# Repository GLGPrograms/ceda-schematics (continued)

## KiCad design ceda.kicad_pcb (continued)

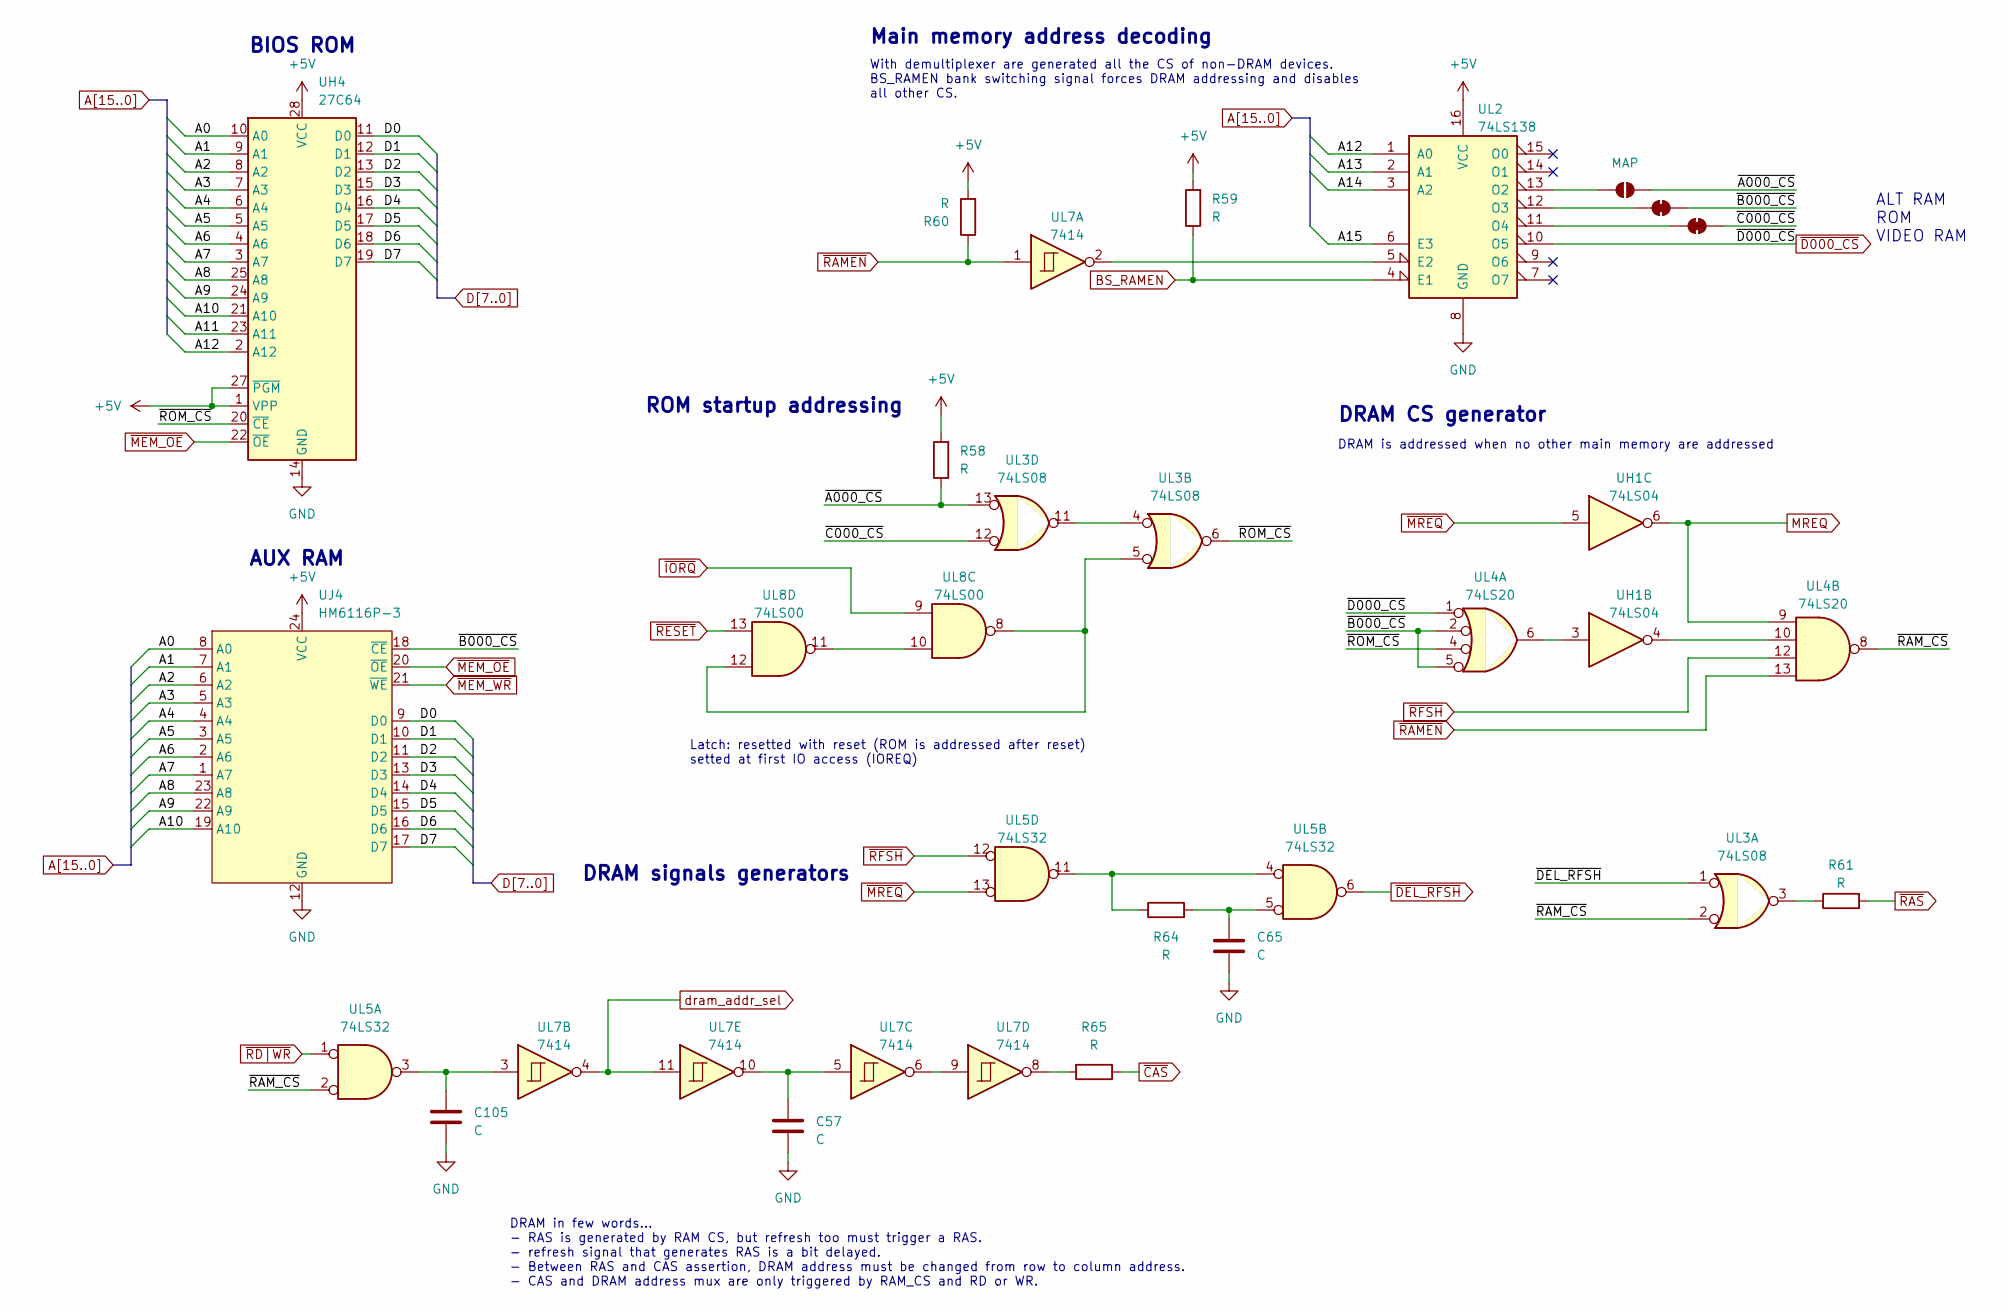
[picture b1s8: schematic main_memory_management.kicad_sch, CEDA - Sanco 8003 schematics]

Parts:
C57, C65, C105: C; C_Disc_D4.3mm_W1.9mm_P5.00mm
JP4: MAP
R58, R59, R60, R61, R64, R65: R; R_Axial_DIN0204_L3.6mm_D1.6mm_P5.08mm_Vertical
UH1: 74LS04; DIP-14_W7.62mm
UH4: 27C64; DIP-28_W15.24mm
UJ4: HM6116P-3; DIP-24_W15.24mm
UL2: 74LS138; DIP-16_W7.62mm
UL3: 74LS08; DIP-14_W7.62mm
UL4: 74LS20; DIP-14_W7.62mm
UL5: 74LS32; DIP-14_W7.62mm
UL7: 7414; DIP-14_W7.62mm
UL8: 74LS00; DIP-14_W7.62mm

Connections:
+5V: R58.2, R59.2, R60.2, UH4.1 (VPP), UH4.27 (~PGM), UH4.28 (VCC), UJ4.24 (VCC), UL2.16 (VCC); also elsewhere on the board
/MainMemoryManagement/~A000_CS: JP4.2 (B), R58.1, UL3.13
/MainMemoryManagement/~B000_CS: JP4.4 (D), UJ4.18 (~CE), UL4.2, UL4.5
/MainMemoryManagement/~C000_CS: JP4.6 (F), UL3.12
/MainMemoryManagement/~RAM_CS: UL3.2, UL4.8, UL5.2
/MainMemoryManagement/~ROM_CS: UH4.20 (~CE), UL3.6, UL4.4
A0: UH4.10 (A0), UJ4.8 (A0); also elsewhere on the board
A1: UH4.9 (A1), UJ4.7 (A1); also elsewhere on the board
A2: UH4.8 (A2), UJ4.6 (A2); also elsewhere on the board
A3: UH4.7 (A3), UJ4.5 (A3); also elsewhere on the board
A4: UH4.6 (A4), UJ4.4 (A4); also elsewhere on the board
A5: UH4.5 (A5), UJ4.3 (A5); also elsewhere on the board
A6: UH4.4 (A6), UJ4.2 (A6); also elsewhere on the board
A7: UH4.3 (A7), UJ4.1 (A7); also elsewhere on the board
A8: UH4.25 (A8), UJ4.23 (A8); also elsewhere on the board
A9: UH4.24 (A9), UJ4.22 (A9); also elsewhere on the board
A10: UH4.21 (A10), UJ4.19 (A10); also elsewhere on the board
A11: UH4.23 (A11); also elsewhere on the board
A12: UH4.2 (A12), UL2.1 (A0); also elsewhere on the board
A13: UL2.2 (A1); also elsewhere on the board
A14: UL2.3 (A2); also elsewhere on the board
A15: UL2.6 (E3); also elsewhere on the board
BS_RAMEN: R59.1, UL2.4 (E1); also elsewhere on the board
D0: UH4.11 (D0), UJ4.9 (D0); also elsewhere on the board
D1: UH4.12 (D1), UJ4.10 (D1); also elsewhere on the board
D2: UH4.13 (D2), UJ4.11 (D2); also elsewhere on the board
D3: UH4.15 (D3), UJ4.13 (D3); also elsewhere on the board
D4: UH4.16 (D4), UJ4.14 (D4); also elsewhere on the board
D5: UH4.17 (D5), UJ4.15 (D5); also elsewhere on the board
D6: UH4.18 (D6), UJ4.16 (D6); also elsewhere on the board
D7: UH4.19 (D7), UJ4.17 (D7); also elsewhere on the board
GND: C57.2, C65.2, C105.2, UH4.14 (GND), UJ4.12 (GND), UL2.8 (GND); also elsewhere on the board
MREQ: UH1.6, UL4.9; also elsewhere on the board
unnamed: C57.1, UL7.5, UL7.10
unnamed: C65.1, R64.2, UL5.5
unnamed: C105.1, UL5.3, UL7.3
unnamed: JP4.1 (A), UL2.13 (O2)
unnamed: JP4.3 (C), UL2.12 (O3)
unnamed: JP4.5 (E), UL2.11 (O4)
unnamed: R61.1, UL3.3
unnamed: R64.1, UL5.4, UL5.11
unnamed: R65.2, UL7.8
unnamed: UH1.3, UL4.6
unnamed: UH1.4, UL4.10
unnamed: UL2.5 (E2), UL7.2
unnamed: UL3.5, UL8.8, UL8.12
unnamed: UL3.4, UL3.11
unnamed: UL7.6, UL7.9
unnamed: UL8.10, UL8.11
dram_addr_sel: UL7.4, UL7.11; also elsewhere on the board
~CAS: R65.1; also elsewhere on the board
~D000_CS: UL2.10 (O5), UL4.1; also elsewhere on the board
~DEL_RFSH: UL3.1, UL5.6
~IORQ: UL8.9; also elsewhere on the board
~MEM_OE: UH4.22 (~OE), UJ4.20 (~OE); also elsewhere on the board
~MEM_WR: UJ4.21 (~WE); also elsewhere on the board
~MREQ: UH1.5, UL5.13; also elsewhere on the board
~RAMEN: R60.1, UL4.13, UL7.1; also elsewhere on the board
~RAS: R61.2; also elsewhere on the board
~RD|WR: UL5.1; also elsewhere on the board
~RESET: UL8.13; also elsewhere on the board
~RFSH: UL4.12, UL5.12; also elsewhere on the board

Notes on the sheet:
Latch: resetted with reset (ROM is addressed after reset) setted at first IO access (IOREQ)
ROM startup addressing
DRAM signals generators
BIOS ROM
DRAM CS generator
DRAM in few words... - RAS is generated by RAM CS, but refresh too must trigger a RAS. - refresh signal that generates RAS is a bit delayed. - Between RAS and CAS assertion, DRAM address must be changed from row to column address. - CAS and DRAM address mux are only triggered by RAM_CS and RD or WR.
With demultiplexer are generated all the CS of non-DRAM devices. BS_RAMEN bank switching signal forces DRAM addressing and disables all other CS.
DRAM is addressed when no other main memory are addressed
ALT RAM ROM VIDEO RAM
AUX RAM
Main memory address decoding

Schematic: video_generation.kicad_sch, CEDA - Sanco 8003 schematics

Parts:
C52, C53: 220p; C_Disc_D4.3mm_W1.9mm_P5.00mm
C54: 47p; C_Disc_D4.3mm_W1.9mm_P5.00mm
D2, D5: D; D_A-405_P5.08mm_Vertical_KathodeUp
J3: Conn_02x06_Odd_Even; PinHeader_2x06_P2.54mm_Vertical
R42: 4.7k; R_Axial_DIN0204_L3.6mm_D1.6mm_P5.08mm_Vertical
R56: 2k2; R_Axial_DIN0309_L9.0mm_D3.2mm_P12.70mm_Horizontal
R57: 4k7; R_Axial_DIN0309_L9.0mm_D3.2mm_P12.70mm_Horizontal
R67, R71, R72, R75: R; R_Axial_DIN0204_L3.6mm_D1.6mm_P5.08mm_Vertical
R68, R69, R73, R74: 470; R_Axial_DIN0204_L3.6mm_D1.6mm_P5.08mm_Vertical
R70, R76: 10; R_Axial_DIN0204_L3.6mm_D1.6mm_P5.08mm_Vertical
R7777: R
RCK1: ContrastKnob
TP4: EXT; TestPoint_Plated_Hole_D2.0mm
TP5: TestPoint
TR4: Q_NPN_BCE; TO-92_Inline_Wide
UE7: CRTC; DIP-40_W15.24mm
UE12: 74LS175; DIP-16_W7.62mm
UE13: 74LS04; DIP-14_W7.62mm
UE15: 74LS32; DIP-14_W7.62mm
UF13: 74LS08; DIP-14_W7.62mm
UH11: 74LS273; DIP-20_W7.62mm
UH12: 2732; DIP-24_W15.24mm
UJ12: 28L22; DIP-20_W7.62mm
UJ13: 74LS86; DIP-14_W7.62mm
UJ14: 74LS166; DIP-16_W7.62mm
UJ15: 74LS161; DIP-16_W7.62mm
UK10: 74LS08; DIP-14_W7.62mm
UK11, UK12: 74LS273; DIP-20_W7.62mm
UK13: 74LS00; DIP-14_W7.62mm
UK14: 74LS10; DIP-14_W7.62mm
UK15: 74LS04; DIP-14_W7.62mm
UL9: 74LS109; DIP-16_W7.62mm
UL10: 74S174; DIP-16_W7.62mm
UL11: 74LS393; DIP-14_W7.62mm
UL12: 74S00; DIP-14_W7.62mm
UL13: 74LS38; DIP-14_W7.62mm
XTAL3: Crystal; Crystal_HC18-U_Horizontal_1EP_style2

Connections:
+5V: R42.1, R67.2, R68.1, R69.1, R75.1, R7777.1, TR4.2 (C), UE7.20 (VCC), UE12.1 (~Mr), UE12.16 (VCC), UH11.1 (~Mr), UH11.20 (VCC), UH12.24 (VCC), UJ12.20 (VCC), UJ14.9 (Clr), UJ14.16 (VCC), UJ15.1 (~MR), UJ15.7 (CEP), UJ15.10 (CET), UJ15.16 (VCC), UK11.1 (~Mr), UK11.20 (VCC), UK12.1 (~Mr), UK12.20 (VCC), UL9.2 (J), UL9.3 (~K), UL9.5 (~S), UL10.16 (VCC); also elsewhere on the board
/VideoGeneration/BEAM: J3.4, R76.2
/VideoGeneration/CONTRAST0: J3.12, R70.2, RCK1.2
/VideoGeneration/CONTRAST1: D5.2 (A), J3.11, R72.1, RCK1.1, UL13.6
/VideoGeneration/HSYNC: J3.8, R68.2, UL13.8
/VideoGeneration/PIXEL_CLK: UJ14.7 (Clk), UJ15.2 (CP), UK15.6, UL10.9 (Cp)
/VideoGeneration/ROM_A5: UJ12.17 (A5), UK11.16 (Q6)
/VideoGeneration/ROM_A6: UJ12.18 (A6), UK11.19 (Q7)
/VideoGeneration/ROM_A7: UJ12.19 (A7), UK11.15 (Q5)
/VideoGeneration/ROM_D5: UJ12.12 (D5), UK12.18 (D7)
/VideoGeneration/ROM_D6: UJ12.13 (D6), UK12.17 (D6)
/VideoGeneration/ROM_D7: UJ12.14 (D7), UK12.14 (D5)
/VideoGeneration/VSYNC: J3.7, R69.2, UL13.11
/VideoGeneration/VSYNC_CRTC: UE7.40 (VSYNC), UE13.9, UL9.4 (C)
/VideoGeneration/attr_blink: UK12.5 (Q1), UK13.5
/VideoGeneration/attr_blink_underline: UK12.15 (Q5), UK13.9
/VideoGeneration/attr_cursor: UK12.6 (Q2), UL10.6 (D2)
/VideoGeneration/attr_cursor_reg: UL10.7 (Q2), UL12.4, UL12.12
/VideoGeneration/attr_invert: UJ13.4, UK12.9 (Q3)
/VideoGeneration/attr_show: UK12.19 (Q7), UK14.11
/VideoGeneration/attr_stretch: UF13.2, UK12.12 (Q4)
/VideoGeneration/attr_underline: UK12.16 (Q6), UK13.12
/VideoGeneration/blink timer: UK13.4, UK13.10, UL11.8 (Q3)
/VideoGeneration/char0: UH11.16 (Q6), UH12.4 (A4)
/VideoGeneration/char1: UH11.2 (Q0), UH12.3 (A5)
/VideoGeneration/char2: UH11.19 (Q7), UH12.2 (A6)
/VideoGeneration/char3: UH11.12 (Q4), UH12.1 (A7)
/VideoGeneration/char4: UH11.9 (Q3), UH12.23 (A8)
/VideoGeneration/char5: UH11.6 (Q2), UH12.22 (A9)
/VideoGeneration/char6: UH11.15 (Q5), UH12.19 (A10)
/VideoGeneration/char7: UH11.5 (Q1), UH12.21 (A11)
/VideoGeneration/cl0: UH12.8 (A0), UJ12.6 (D0)
/VideoGeneration/cl1: UH12.7 (A1), UJ12.7 (D1)
/VideoGeneration/cl2: UH12.6 (A2), UJ12.8 (D2)
/VideoGeneration/cl3: UH12.5 (A3), UJ12.9 (D3)
/VideoGeneration/crt3: J3.3, R75.2, UL13.1
/VideoGeneration/crt5: J3.5, UL12.3, UL13.2
/VideoGeneration/cudisp: UE7.19 (CUDISP), UE12.12 (D2)
/VideoGeneration/cudisp_int: UE12.10 (Q2), UE12.13 (D3)
/VideoGeneration/cudisp_reg: UE12.15 (Q3), UJ13.10
/VideoGeneration/disptmg: UE7.18 (DISPTMG), UE12.4 (D0), UK10.4
/VideoGeneration/disptmg_ancorpiureg: UK10.1, UL10.5 (Q1)
/VideoGeneration/disptmg_int: UE12.2 (Q0), UE12.5 (D1)
/VideoGeneration/dot pattern: UJ14.13 (Qh), UK14.10
/VideoGeneration/pixel: UJ13.8, UL10.3 (D0)
/VideoGeneration/pixel_reg: UK10.2, UL10.2 (Q0)
/VideoGeneration/pixel_valid: UK10.3, UL12.2, UL12.13
/VideoGeneration/ra0: UE7.38 (RA0), UJ12.1 (A0)
/VideoGeneration/ra1: UE7.37 (RA1), UJ12.2 (A1)
/VideoGeneration/ra2: UE7.36 (RA2), UJ12.3 (A2)
/VideoGeneration/ra3: UE7.35 (RA3), UJ12.4 (A3)
/VideoGeneration/ra4: UE7.34 (RA4), UJ12.5 (A4)
/VideoGeneration/stretch: UK11.12 (Q4), UK12.13 (D4), UK15.1
/VideoGeneration/~CHAR_EN: UJ14.15 (PE), UJ15.9 (~PE), UK12.11 (Cp), UK15.10
/VideoGeneration/~VSYNC_CRTC: UE13.8, UL11.1 (CP), UL13.12, UL13.13
/VideoGeneration/~cudisp_reg: UE12.14 (~Q3), UL12.5
/VideoGeneration/~pixel_cursor: J3.6, UL12.11, UL13.4, UL13.5
A0: UE7.24 (RS); also elsewhere on the board
CRTC_CLK: TP5.1, UE7.21 (CLK), UJ15.12 (Q2), UK15.9; also elsewhere on the board
D0: UE7.33 (D0); also elsewhere on the board
D1: UE7.32 (D1); also elsewhere on the board
D2: UE7.31 (D2); also elsewhere on the board
D3: UE7.30 (D3); also elsewhere on the board
D4: UE7.29 (D4); also elsewhere on the board
D5: UE7.28 (D5); also elsewhere on the board
D6: UE7.27 (D6); also elsewhere on the board
D7: UE7.26 (D7); also elsewhere on the board
FRAME_SYNC: UL9.6 (Q); also elsewhere on the board
GND: C52.2, C53.2, J3.1, J3.2, J3.9, J3.10, R57.1, R70.1, R71.2, R72.2, R73.2, R74.2, UE7.1 (VSS), UE12.8 (GND), UH11.10 (GND), UH12.12 (GND), UH12.18 (~CE), UH12.20 (~OE), UJ12.10 (GND), UJ12.15 (~G1), UJ12.16 (~G2), UJ14.1 (Ds), UJ14.8 (GND), UJ15.3 (D0), UJ15.4 (D1), UJ15.5 (D2), UJ15.8 (GND), UK11.10 (GND), UK12.10 (GND), UL10.8 (GND), UL11.2 (MR), UL11.12 (MR); also elsewhere on the board
unnamed: C52.1, C54.2, R56.2, R57.2, UK15.3
unnamed: C53.1, R56.1, UK15.4, UK15.5, XTAL3.2
unnamed: C54.1, XTAL3.1
unnamed: D2.2 (A), R71.1, UL13.3
unnamed: D2.1 (K), D5.1 (K), R73.1, R7777.2, TR4.3 (B)
unnamed: R74.1, R76.1, TR4.1 (E)
unnamed: UE7.23 (E), UE13.10
unnamed: UE7.39 (HSYNC), UE13.1
unnamed: R42.2, UE7.3 (LPSTB)
unnamed: UE13.2, UL13.9, UL13.10
unnamed: UE13.11, UE13.12
unnamed: UE13.13, UK13.3
unnamed: UF13.1, UK15.12
unnamed: UH12.9 (D0), UJ14.2 (A)
unnamed: UH12.10 (D1), UJ14.3 (B)
unnamed: UH12.11 (D2), UJ14.4 (C)
unnamed: UH12.13 (D3), UJ14.5 (D)
unnamed: UH12.14 (D4), UJ14.10 (E)
unnamed: UH12.15 (D5), UJ14.11 (F)
unnamed: UH12.16 (D6), UJ14.12 (G)
unnamed: UH12.17 (D7), UJ14.14 (H)
unnamed: UJ13.5, UK14.6
unnamed: UJ13.6, UJ13.9
unnamed: UF13.3, UJ14.6 (CE)
unnamed: UJ15.6 (D3), UK15.2
unnamed: UJ15.15 (TC), UK15.11
unnamed: UK10.6, UK11.13 (D4)
unnamed: TP4.1, UK11.2 (Q0)
unnamed: UK11.5 (Q1), UK12.4 (D1)
unnamed: UK11.6 (Q2), UK12.7 (D2)
unnamed: UK11.9 (Q3), UK12.8 (D3)
unnamed: UK13.6, UK14.9
unnamed: UK13.11, UK14.4
unnamed: UK13.8, UK13.13
unnamed: UK14.3, UK14.5, UK14.8
unnamed: UE15.8, UL9.1 (~R)
unnamed: R67.1, UL10.1 (~Mr)
unnamed: UL11.3 (Q0), UL11.13 (CP)
unnamed: UL12.1, UL12.6
VMA0: UE7.4 (MA0); also elsewhere on the board
VMA1: UE7.5 (MA1); also elsewhere on the board
VMA2: UE7.6 (MA2); also elsewhere on the board
VMA3: UE7.7 (MA3); also elsewhere on the board
VMA4: UE7.8 (MA4); also elsewhere on the board
VMA5: UE7.9 (MA5); also elsewhere on the board
VMA6: UE7.10 (MA6); also elsewhere on the board
VMA7: UE7.11 (MA7); also elsewhere on the board
VMA8: UE7.12 (MA8); also elsewhere on the board
VMA9: UE7.13 (MA9); also elsewhere on the board
VMA10: UE7.14 (MA10); also elsewhere on the board
attrmd0: UK11.8 (D3); also elsewhere on the board
attrmd1: UK11.4 (D1); also elsewhere on the board
attrmd2: UK11.7 (D2); also elsewhere on the board
attrmd3: UK10.5; also elsewhere on the board
attrmd4: UK11.17 (D6); also elsewhere on the board
attrmd5: UK11.18 (D7); also elsewhere on the board
attrmd6: UK11.14 (D5); also elsewhere on the board
attrmd7: UK11.3 (D0); also elsewhere on the board
chmd0: UH11.17 (D6); also elsewhere on the board
chmd1: UH11.3 (D0); also elsewhere on the board
chmd2: UH11.18 (D7); also elsewhere on the board
chmd3: UH11.13 (D4); also elsewhere on the board
chmd4: UH11.8 (D3); also elsewhere on the board
chmd5: UH11.7 (D2); also elsewhere on the board
chmd6: UH11.14 (D5); also elsewhere on the board
chmd7: UH11.4 (D1); also elsewhere on the board
disptmg_reg: UE12.7 (Q1), UL10.4 (D1); also elsewhere on the board
half_pxclk: UJ15.14 (Q0), UK15.13; also elsewhere on the board
quart_pxclk: UJ15.13 (Q1); also elsewhere on the board
~CRTC_CLK: UE12.9 (Cp), UH11.11 (Cp), UK11.11 (Cp), UK15.8; also elsewhere on the board
~CRTC_CS: UE7.25 (~CS), UE15.9; also elsewhere on the board
~IO_OE: UE15.10, UK13.2; also elsewhere on the board
~IO_WR: UE7.22 (R/~W), UK13.1; also elsewhere on the board
~RESET: UE7.2 (~RES); also elsewhere on the board

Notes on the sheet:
Always enabled and never resetted
underline is generated by attribute index (attributes 4-6). It can add underline, overline, both, or a blinking underline (combined with blink_underline signal). Note that "underline" is not affected by "blink" nor "show", hereby the presence of blink_underline.
Toggle pixels when cursor has to be shown. If characher is inverted, cursor is inverted too.
Pixel clock generator
Counter
Character Line Index
Last stage of pipeline: pixel is registered. To keep signals in sync with the pipeline, the signals used in this last stage are delayed. Why cudisp is not delayed? We don't know.
Then, character is sampled for each character in J14 shift register. Attributes are sampled for each character in register K12. Note: ~{CHAR_EN} period is doubled when horizontal stretch is requested. For this reason both attributes and character must be freezed with PIXEL_EN.
Invert is attribute 0: when is set, frame is displayed in inverted colors.
Wired OR. Transistor base is pulled up (i.e. BEAM is pulled up) if L13B is HIGH or L13A is HIGH.
All RAMs outputs (both char and attr) are syncronized on negative edge of CRTC_CLK.
blink is attribute 1: - when 0, it gates blink_timer and dot_pattern is not affected. - when 1, blink_timer can gate dot_pattern, making the character appear and disappear. blink_timer is a square wave obtained from VSYNC / 32 ~ 1.28s
Character clock generator
This latch is used to generate a syncronization signal, set by the VSYNC from CRTC, resetted by a read access to CRTC from Z80.
Character Line Pattern
Both disptmg and cudisp must be delayed to be in sync with the pipeline. At the output of J14, a double CRTC_CLK delay is needed.
(pixel_reg and disptmg) and attr_cursor or (pixel_reg and disptmg) and (~attr_cursor or cudisp)
show is generated by attribute index (attributes 4-6). It is always set, unless if index=100.
Raster address
1/32 VSYNC ~ 1.28s
Blink generator
Attribute Memory Data
Char ROM
Character Memory Data
1.875MHz
Video memory Address
All video data occurring during blanking time must be ignored. DISPTMG is 0 during blanking time.
Handling horizontal stretch attribute: - When stretch attribute is 0, the shift register is always enabled; - When stretch attribute is 1, the shift register is enabled one clock in two.
174

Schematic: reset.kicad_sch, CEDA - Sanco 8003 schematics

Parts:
C12, C14, C15, C36: C; C_Disc_D4.3mm_W1.9mm_P5.00mm
C40: 10n; C_Disc_D4.3mm_W1.9mm_P5.00mm
C55: C_Polarized; CP_Radial_D5.0mm_P2.50mm
D3: D; D_A-405_P5.08mm_Vertical_KathodeUp
J4: MAINCLK
R17, R023, R41, R44, R63: R; R_Axial_DIN0204_L3.6mm_D1.6mm_P5.08mm_Vertical
R55: 10k; R_Axial_DIN0309_L9.0mm_D3.2mm_P12.70mm_Horizontal
UA6: 74LS161; DIP-16_W7.62mm
UA7: 74LS04; DIP-14_W7.62mm
UD3: 7406; DIP-14_W7.62mm
UD14: 74LS32; DIP-14_W7.62mm
UF16: 74LS04; DIP-14_W7.62mm
UH15: 74LS74; DIP-14_W7.62mm
UH16: 74LS123; DIP-16_W7.62mm
UL7: 7414; DIP-14_W7.62mm
XTAL1: 16M; Crystal_HC18-U_Vertical

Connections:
+5V: C12.2, C15.2, D3.1 (K), R41.1, R44.1, R55.1, R63.2, UA6.1 (~MR), UA6.9 (~PE), UA6.16 (VCC), UH15.2 (D), UH15.4 (~S), UH16.11 (Clr); also elsewhere on the board
/Reset/BTN_RESET: UD14.9, UH16.5 (Q)
/Reset/POR: UD14.10, UL7.12
CPU_CLK: UA7.12; also elsewhere on the board
EXBUS_CLK: UA7.10; also elsewhere on the board
FDC_CLK: UA7.6; also elsewhere on the board
GND: C36.2, C55.2, R023.2, UA6.3 (D0), UA6.4 (D1), UA6.5 (D2), UA6.6 (D3), UA6.8 (GND), UH16.9 (A); also elsewhere on the board
unnamed: C12.1, R17.2, UA7.1, UA7.4, XTAL1.1
unnamed: C14.1, XTAL1.2
unnamed: C14.2, C15.1, R17.1, R023.1, UA7.3
unnamed: C55.1, D3.2 (A), R63.1, UL7.13
unnamed: J4.4 (A0), UA7.5
unnamed: J4.2 (A1), UA6.14 (Q0)
unnamed: J4.1 (B1), UA6.13 (Q1), UA7.11, UA7.13
unnamed: UA6.2 (CP), UA7.2
unnamed: UD3.9, UD14.8
unnamed: UF16.6, UH15.3 (C)
unnamed: UH15.5 (Q), UH16.10 (B)
unnamed: UF16.12, UH15.1 (~R)
unnamed: C40.2, UH16.6 (Cext)
unnamed: C40.1, R55.2, UH16.7 (RCext)
RESET: UF16.10; also elsewhere on the board
~M1: UF16.5; also elsewhere on the board
~RESET_BTN: C36.1, R44.2, UF16.13; also elsewhere on the board
~RESET: R41.2, UD3.8, UF16.11; also elsewhere on the board

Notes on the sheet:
Generates a single reset pulse when signal on B input is asserted. Reset pulse width is 30us long.
Reset circuit
Button reset is syncronized with Z80 opcode fetch (M1)
This should be just R23, but KiCAD complains about it
Power On Reset POR is asserted while capacitor voltage is below VIH of 7414. Diode makes the capacitor discharge faster on power off.
Pushbutton signal from daughterboard
Main clock circuit

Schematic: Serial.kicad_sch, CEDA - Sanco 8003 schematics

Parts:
C16, C17, C18, C19, C29, C30, C31: 330p; C_Disc_D4.3mm_W1.9mm_P5.00mm
C28: 330p; C_Disc_D4.3mm_W1.9mm_P5.00mm; not fitted
J5: SIOCLK; PinHeader_2x03_P2.54mm_Vertical
JP3: KB_SEL; PinHeader_2x01_P2.54mm_Vertical
R40, R79: 4k7; R_Axial_DIN0204_L3.6mm_D1.6mm_P5.08mm_Vertical
UA15: SN75189; DIP-14_W7.62mm
UB9: 74LS04; DIP-14_W7.62mm
UC2: 7417; DIP-14_W7.62mm
UC10: Z8440/2 (SIO/2); DIP-40_W15.24mm
UC15: DIP-14_W7.62mm
UD14: 74LS32; DIP-14_W7.62mm
UD15, UD16: SN75188; DIP-14_W7.62mm

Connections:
+5V: R40.1, R79.2; also elsewhere on the board
+12V: UD15.14 (VCC+), UD16.14 (VCC+); also elsewhere on the board
-12V: UD15.1 (VCC-), UD16.1 (VCC-); also elsewhere on the board
/Serial/RxCA: J5.2 (A0), UC10.13 (~RxCA)
/Serial/RxCA': J5.1 (A1), UA15.11
/Serial/RxDA: UC10.12 (RxDA), UC15.3
/Serial/RxDB: UC10.29 (RxDB), UD14.11
/Serial/TxCA: J5.4 (B0), J5.6 (C0), UC10.14 (~TxCA)
/Serial/TxCA': J5.3 (B1), UA15.8
/Serial/TxDA: UC10.15 (TxDA), UD15.2
/Serial/TxDB: UC10.26 (TxDB), UD14.1, UD14.4
/Serial/~CTSA: UC10.18 (~CTSA), UC15.6
/Serial/~CTSB: UA15.6, UC10.23 (~CTSB)
/Serial/~DCDA: UC10.19 (~DCDA), UC15.8
/Serial/~DCDB: UA15.3, UC10.22 (~DCDB)
/Serial/~DTRA: UC10.16 (~DTRA), UD15.9, UD15.10
/Serial/~DTRB: UB9.9, UC10.25 (~DTRB), UD14.2
/Serial/~RTSA: UC10.17 (~RTSA), UD15.4, UD15.5
A0: UC10.33 (C/~D); also elsewhere on the board
A1: UC10.34 (B/~A); also elsewhere on the board
CPU_CLK: UC10.20 (CLK); also elsewhere on the board
D0: UC10.40 (D0); also elsewhere on the board
D1: UC10.1 (D1); also elsewhere on the board
D2: UC10.39 (D2); also elsewhere on the board
D3: UC10.2 (D3); also elsewhere on the board
D4: UC10.38 (D4); also elsewhere on the board
D5: UC10.3 (D5); also elsewhere on the board
D6: UC10.37 (D6); also elsewhere on the board
D7: UC10.4 (D7); also elsewhere on the board
GND: C16.1, C17.1, C18.1, C19.1, C28.1, C29.1, C30.1, C31.1, UC10.31 (GND), UD15.7 (GND), UD16.7 (GND); also elsewhere on the board
KBD_CLK: UC10.27 (~TxCB), UC10.28 (~RxCB); also elsewhere on the board
KBD_RX: JP3.2 (B), R79.1, UC2.6; also elsewhere on the board
KBD_TX: JP3.1 (A), R40.2, UD14.12, UD14.13; also elsewhere on the board
unnamed: C16.2, UA15.9
unnamed: C17.2, UA15.2
unnamed: C18.2, UA15.12
unnamed: C19.2, UA15.5
unnamed: C28.2, UC15.12
unnamed: C29.2, UC15.9
unnamed: C30.2, UC15.5
unnamed: C31.2, UC15.2
unnamed: UB9.8, UD14.5
unnamed: UC2.5, UD14.3
unnamed: UD14.6, UD16.2
PRNT_1: UD16.3; also elsewhere on the board
PRNT_3: UA15.4; also elsewhere on the board
PRNT_4: UA15.1; also elsewhere on the board
SER_2: UD15.3; also elsewhere on the board
SER_3: UC15.1; also elsewhere on the board
SER_4: UD15.6; also elsewhere on the board
SER_5: UC15.4; also elsewhere on the board
SER_6: UC15.10; also elsewhere on the board
SER_15: UA15.10; also elsewhere on the board
SER_17: UA15.13; also elsewhere on the board
SER_20: UD15.8; also elsewhere on the board
SER_24: UD15.11; also elsewhere on the board
SER_CLK: J5.5 (C1), UD15.12, UD15.13; also elsewhere on the board
~IE_0: UC10.6 (IEI)
~IE_1: UC10.7 (IEO); also elsewhere on the board
~INT: UC10.5 (~INT); also elsewhere on the board
~IORQ: UC10.36 (~IORQ); also elsewhere on the board
~M1: UC10.8 (~M1); also elsewhere on the board
~RD: UC10.32 (~RD); also elsewhere on the board
~RESET: UC10.21 (~RESET); also elsewhere on the board
~SIO_CS: UC10.35 (~CE); also elsewhere on the board

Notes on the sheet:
RS-232 UART
153.6 kHz
Open Collector
Standard RS-232 with +/-12V logic levels, hardware flux control support, syncronous serial support. As default, UART timebase is generated by CTC and provided both to SIO (RxCA and TxCA) and to device (TxCA''). This setting may be changed by using SIOCLK jumpers.
Supplementary UART
Keyboard UART
CEDA keyboard UART has a double usage, since when DTR is asserted the communication with keyboard is disabled and data is transmitted on PRNT connector. The device connected to PRNT may signal its presence (DCD) or suspend data flow (CTS). The device can't send data to the CEDA, so except for the f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
CEDA keyboard communicates by TTL UART, half duplex, open collector. Timebase is generated by CTC, as default set to 9600 baud. RX and TX lines are shorted on board. TX is disabled when DTR is asserted.

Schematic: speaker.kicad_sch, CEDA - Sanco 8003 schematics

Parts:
C22: 4.7u; CP_Radial_D5.0mm_P2.50mm
C23, C25, C32: 10n; C_Disc_D4.3mm_W1.9mm_P5.00mm
LS0: Speaker
R36, R38: 37k; R_Axial_DIN0204_L3.6mm_D1.6mm_P5.08mm_Vertical
R37: 33k; R_Axial_DIN0204_L3.6mm_D1.6mm_P5.08mm_Vertical
R78: 33; R_Axial_DIN0309_L9.0mm_D3.2mm_P12.70mm_Horizontal
RM2: R_Network08; R_Array_SIP9
SP-Plug1: Molex_KK-254_AE-6410-02A_1x02_P2.54mm_Vertical
SP-Socket1: SpeakerConnector
SW1: SW_DIP_x08; SW_DIP_SPSTx08_Slide_9.78x22.5mm_W7.62mm_P2.54mm
UA11: 74LS541; DIP-20_W7.62mm
UC7: LM556; DIP-14_W7.62mm
UD8, UD9: 74LS138; DIP-16_W7.62mm
UF16: 74LS04; DIP-14_W7.62mm

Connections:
+5V: R37.1, R38.1, R78.2, RM2.1 (common), UA11.20 (VCC), UC7.4 (R), UC7.14 (VCC), UD8.16 (VCC), UD9.16 (VCC); also elsewhere on the board
/IO space/~DIPSW_CS: UA11.1 (G1), UD8.12 (O3)
/IO space/~SPEAKER_CS: UC7.6 (TR), UD8.10 (O5)
A1: UD8.1 (A0); also elsewhere on the board
A2: UD8.2 (A1); also elsewhere on the board
A3: UD8.3 (A2); also elsewhere on the board
A4: UD9.1 (A0); also elsewhere on the board
A5: UD9.2 (A1); also elsewhere on the board
A6: UD9.3 (A2); also elsewhere on the board
A7: UD9.6 (E3); also elsewhere on the board
D0: UA11.18 (Y0); also elsewhere on the board
D1: UA11.17 (Y1); also elsewhere on the board
D2: UA11.16 (Y2); also elsewhere on the board
D3: UA11.15 (Y3); also elsewhere on the board
D4: UA11.14 (Y4); also elsewhere on the board
D5: UA11.13 (Y5); also elsewhere on the board
D6: UA11.12 (Y6); also elsewhere on the board
D7: UA11.11 (Y7); also elsewhere on the board
GND: C22.2, C23.1, C25.1, C32.2, SW1.1, SW1.2, SW1.3, SW1.4, SW1.5, SW1.6, SW1.7, SW1.8, UA11.10 (GND), UC7.7 (GND), UD8.8 (GND), UD9.4 (E1), UD9.5 (E2), UD9.8 (GND); also elsewhere on the board
unnamed: LS0.1, SP-Socket1.2
unnamed: LS0.2, SP-Socket1.1
unnamed: RM2.2 (R1), SW1.9, UA11.2 (A0)
unnamed: RM2.3 (R2), SW1.10, UA11.3 (A1)
unnamed: RM2.4 (R3), SW1.11, UA11.4 (A2)
unnamed: RM2.5 (R4), SW1.12, UA11.5 (A3)
unnamed: RM2.6 (R5), SW1.13, UA11.6 (A4)
unnamed: RM2.7 (R6), SW1.14, UA11.7 (A5)
unnamed: RM2.8 (R7), SW1.15, UA11.8 (A6)
unnamed: SP-Plug1.1, UC7.9 (Q)
unnamed: R78.1, SP-Plug1.2
unnamed: C25.2, UC7.3 (CV)
unnamed: C22.1, R38.2, UC7.1 (DIS), UC7.2 (THR)
unnamed: UC7.5 (Q), UC7.10 (R)
unnamed: C23.2, UC7.11 (CV)
unnamed: R36.2, R37.2, UC7.13 (DIS)
unnamed: C32.1, R36.1, UC7.8 (TR), UC7.12 (THR)
unnamed: UD8.5 (E2), UD9.10 (O5)
unnamed: UD8.6 (E3), UF16.4
disptmg_reg: UA11.9 (A7); also elsewhere on the board
~CRTC_CS: UD9.13 (O2); also elsewhere on the board
~CTC_CS: UD9.9 (O6); also elsewhere on the board
~FDC_CS: UD9.11 (O4); also elsewhere on the board
~FDC_TC: UD8.9 (O6); also elsewhere on the board
~GPIO_CS: UD9.15 (O0); also elsewhere on the board
~IORQ: UF16.3; also elsewhere on the board
~MysteriousTrigger_CS: UD8.11 (O4); also elsewhere on the board
~PerrorReset_CS: UD8.7 (O7); also elsewhere on the board
~PrinterReset_CS: UD8.14 (O1); also elsewhere on the board
~PrinterSet_CS: UD8.15 (O0); also elsewhere on the board
~RD|WR: UD8.4 (E1); also elsewhere on the board
~RD: UA11.19 (G2); also elsewhere on the board
~SIO_CS: UD9.12 (O3); also elsewhere on the board

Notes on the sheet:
Big IO
0xDC FDC Terminal Count
DIP switch IO = 0xD6
IO address space multiplexing Each IO device has 4 address bits reserved. The other 4 bits are used to partition the addressing space. Small IO addressing space has 1 bit for each peripheral (i.e. 2 address) but most of them use only one address.
DIP Switch is set to 0x0E. It contains the configuration of the SIO baudrate.
0xD- small IO
0xD6 DIP Switch
f = 1.3kHz
0xDA speaker
t = 120ms
0x9- unused?
0xF- unused?
0xE- CTC
0xA- CRTC
Speaker IO = 0xDA
0xDE parity error reset
0xD2 handshake on PRN connector (reset)
0xD8 trigger CTC
0xD0 handshake on PRN connector (set)
0xD4 unused?
Small IO
0x8- 8255 GPIO
0xC- FDC
0xB- SIO

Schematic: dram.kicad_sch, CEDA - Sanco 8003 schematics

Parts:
C106: C; C_Disc_D4.3mm_W1.9mm_P5.00mm
PARITY1: LED; LED_D3.0mm
R46, R62: R; R_Axial_DIN0204_L3.6mm_D1.6mm_P5.08mm_Vertical
R47, R48, R49, R50, R51, R52, R53, R54: R_Small; R_Axial_DIN0204_L3.6mm_D1.6mm_P5.08mm_Vertical
R66: 470; R_Axial_DIN0204_L3.6mm_D1.6mm_P5.08mm_Vertical
UH7: 74LS04; DIP-14_W7.62mm
UJ2, UJ3: 74157; DIP-16_W7.62mm
UJ7: 74LS280; DIP-14_W7.62mm
UK1, UK2, UK3, UK4, UK5, UK6, UK7, UK8, UK9: 4164; DIP-16_W7.62mm
UK10: 74LS08; DIP-14_W7.62mm
UL5: 74LS32; DIP-14_W7.62mm
UL8: 74LS00; DIP-14_W7.62mm
UL9: 74LS109; DIP-16_W7.62mm

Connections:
+5V: R46.2, R66.2, UJ2.16 (VCC), UJ3.16 (VCC), UJ7.14 (VCC), UK1.8 (VDD), UK2.8 (VDD), UK3.8 (VDD), UK4.8 (VDD), UK5.8 (VDD), UK6.8 (VDD), UK7.8 (VDD), UK8.8 (VDD), UK9.8 (VDD), UL9.11 (~S), UL9.13 (~K); also elsewhere on the board
/DRAM and parity/NC: R46.1, UK1.1 (NC), UK2.1 (NC), UK3.1 (NC), UK4.1 (NC), UK5.1 (NC), UK6.1 (NC), UK7.1 (NC), UK8.1 (NC), UK9.1 (NC)
/DRAM and parity/RA0: R47.1, UK1.5 (A0), UK2.5 (A0), UK3.5 (A0), UK4.5 (A0), UK5.5 (A0), UK6.5 (A0), UK7.5 (A0), UK8.5 (A0), UK9.5 (A0)
/DRAM and parity/RA1: R49.1, UK1.7 (A1), UK2.7 (A1), UK3.7 (A1), UK4.7 (A1), UK5.7 (A1), UK6.7 (A1), UK7.7 (A1), UK8.7 (A1), UK9.7 (A1)
/DRAM and parity/RA2: R48.1, UK1.6 (A2), UK2.6 (A2), UK3.6 (A2), UK4.6 (A2), UK5.6 (A2), UK6.6 (A2), UK7.6 (A2), UK8.6 (A2), UK9.6 (A2)
/DRAM and parity/RA3: R53.1, UK1.12 (A3), UK2.12 (A3), UK3.12 (A3), UK4.12 (A3), UK5.12 (A3), UK6.12 (A3), UK7.12 (A3), UK8.12 (A3), UK9.12 (A3)
/DRAM and parity/RA4: R52.1, UK1.11 (A4), UK2.11 (A4), UK3.11 (A4), UK4.11 (A4), UK5.11 (A4), UK6.11 (A4), UK7.11 (A4), UK8.11 (A4), UK9.11 (A4)
/DRAM and parity/RA5: R51.1, UK1.10 (A5), UK2.10 (A5), UK3.10 (A5), UK4.10 (A5), UK5.10 (A5), UK6.10 (A5), UK7.10 (A5), UK8.10 (A5), UK9.10 (A5)
/DRAM and parity/RA6: R54.1, UK1.13 (A6), UK2.13 (A6), UK3.13 (A6), UK4.13 (A6), UK5.13 (A6), UK6.13 (A6), UK7.13 (A6), UK8.13 (A6), UK9.13 (A6)
/DRAM and parity/RA7: R50.1, UK1.9 (A7), UK2.9 (A7), UK3.9 (A7), UK4.9 (A7), UK5.9 (A7), UK6.9 (A7), UK7.9 (A7), UK8.9 (A7), UK9.9 (A7)
/DRAM and parity/parity_d: UJ7.5 (Even), UK9.2 (DI), UL9.14 (J)
/DRAM and parity/parity_q: UK9.14 (DO), UK10.12
/DRAM and parity/~DRAM_WE: R62.2, UK1.3 (~WE), UK2.3 (~WE), UK3.3 (~WE), UK4.3 (~WE), UK5.3 (~WE), UK6.3 (~WE), UK7.3 (~WE), UK8.3 (~WE), UK9.3 (~WE)
A0: UJ3.2 (I0a); also elsewhere on the board
A1: UJ3.5 (I0b); also elsewhere on the board
A2: UJ3.11 (I0c); also elsewhere on the board
A3: UJ3.14 (I0d); also elsewhere on the board
A4: UJ2.2 (I0a); also elsewhere on the board
A5: UJ2.5 (I0b); also elsewhere on the board
A6: UJ2.11 (I0c); also elsewhere on the board
A7: UJ3.3 (I1a); also elsewhere on the board
A8: UJ3.6 (I1b); also elsewhere on the board
A9: UJ3.10 (I1c); also elsewhere on the board
A10: UJ3.13 (I1d); also elsewhere on the board
A11: UJ2.3 (I1a); also elsewhere on the board
A12: UJ2.6 (I1b); also elsewhere on the board
A13: UJ2.10 (I1c); also elsewhere on the board
A14: UJ2.14 (I0d); also elsewhere on the board
A15: UJ2.13 (I1d); also elsewhere on the board
D0: UJ7.8 (A), UK1.2 (DI), UK1.14 (DO); also elsewhere on the board
D1: UJ7.9 (B), UK2.2 (DI), UK2.14 (DO); also elsewhere on the board
D2: UJ7.10 (C), UK3.2 (DI), UK3.14 (DO); also elsewhere on the board
D3: UJ7.11 (D), UK4.2 (DI), UK4.14 (DO); also elsewhere on the board
D4: UJ7.12 (E), UK5.2 (DI), UK5.14 (DO); also elsewhere on the board
D5: UJ7.13 (F), UK6.2 (DI), UK6.14 (DO); also elsewhere on the board
D6: UJ7.1 (G), UK7.2 (DI), UK7.14 (DO); also elsewhere on the board
D7: UJ7.2 (H), UK8.2 (DI), UK8.14 (DO); also elsewhere on the board
GND: C106.2, UJ2.8 (GND), UJ2.15 (E), UJ3.8 (GND), UJ3.15 (E), UJ7.7 (GND), UK1.16 (GND), UK2.16 (GND), UK3.16 (GND), UK4.16 (GND), UK5.16 (GND), UK6.16 (GND), UK7.16 (GND), UK8.16 (GND), UK9.16 (GND); also elsewhere on the board
unnamed: PARITY1.2 (A), R66.1
unnamed: PARITY1.1 (K), UL9.9 (~Q)
unnamed: R62.1, UL5.8
unnamed: UH7.8, UL8.5
unnamed: R52.2, UJ2.4 (Za)
unnamed: R51.2, UJ2.7 (Zb)
unnamed: R54.2, UJ2.9 (Zc)
unnamed: R50.2, UJ2.12 (Zd)
unnamed: R47.2, UJ3.4 (Za)
unnamed: R49.2, UJ3.7 (Zb)
unnamed: R48.2, UJ3.9 (Zc)
unnamed: R53.2, UJ3.12 (Zd)
unnamed: UJ7.4 (I), UK10.11
unnamed: C106.1, UL8.6, UL9.12 (C)
unnamed: UK10.8, UL9.15 (~R)
PERROR: UL9.10 (Q); also elsewhere on the board
dram_addr_sel: UJ2.1 (S), UJ3.1 (S), UL8.4; also elsewhere on the board
~CAS: UK1.15 (~CAS), UK2.15 (~CAS), UK3.15 (~CAS), UK4.15 (~CAS), UK5.15 (~CAS), UK6.15 (~CAS), UK7.15 (~CAS), UK8.15 (~CAS), UK9.15 (~CAS); also elsewhere on the board
~PerrorReset_CS: UK10.9; also elsewhere on the board
~RAS: UK1.4 (~RAS), UK2.4 (~RAS), UK3.4 (~RAS), UK4.4 (~RAS), UK5.4 (~RAS), UK6.4 (~RAS), UK7.4 (~RAS), UK8.4 (~RAS), UK9.4 (~RAS); also elsewhere on the board
~RD: UH7.9; also elsewhere on the board
~RESET: UK10.10; also elsewhere on the board
~WR: UK10.13, UL5.9, UL5.10; also elsewhere on the board

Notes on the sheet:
DRAM addressing in brief: RAS, dram_addr_sel and CAS are generated in memory management sheet. - DRAM is organized as a square matrix, so its 64k addressing space is splitted in 8 address bits used both for row and column address. 2^8 * 2^8 = 64k. - RAS is used to sample RA (RAM Address) as row add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
- generated parity is fed into Din of a separate DRAM memory IC. - stored parity parity_q (Dout) is fed into generator/validator only during memory reads. - while validating, parity_d = parity error. Its value is registered in xxx latch and makes a LED turn on (and probably send an IRQ to Z80?)
TODO: place R values
Enabled only during DRAM reads

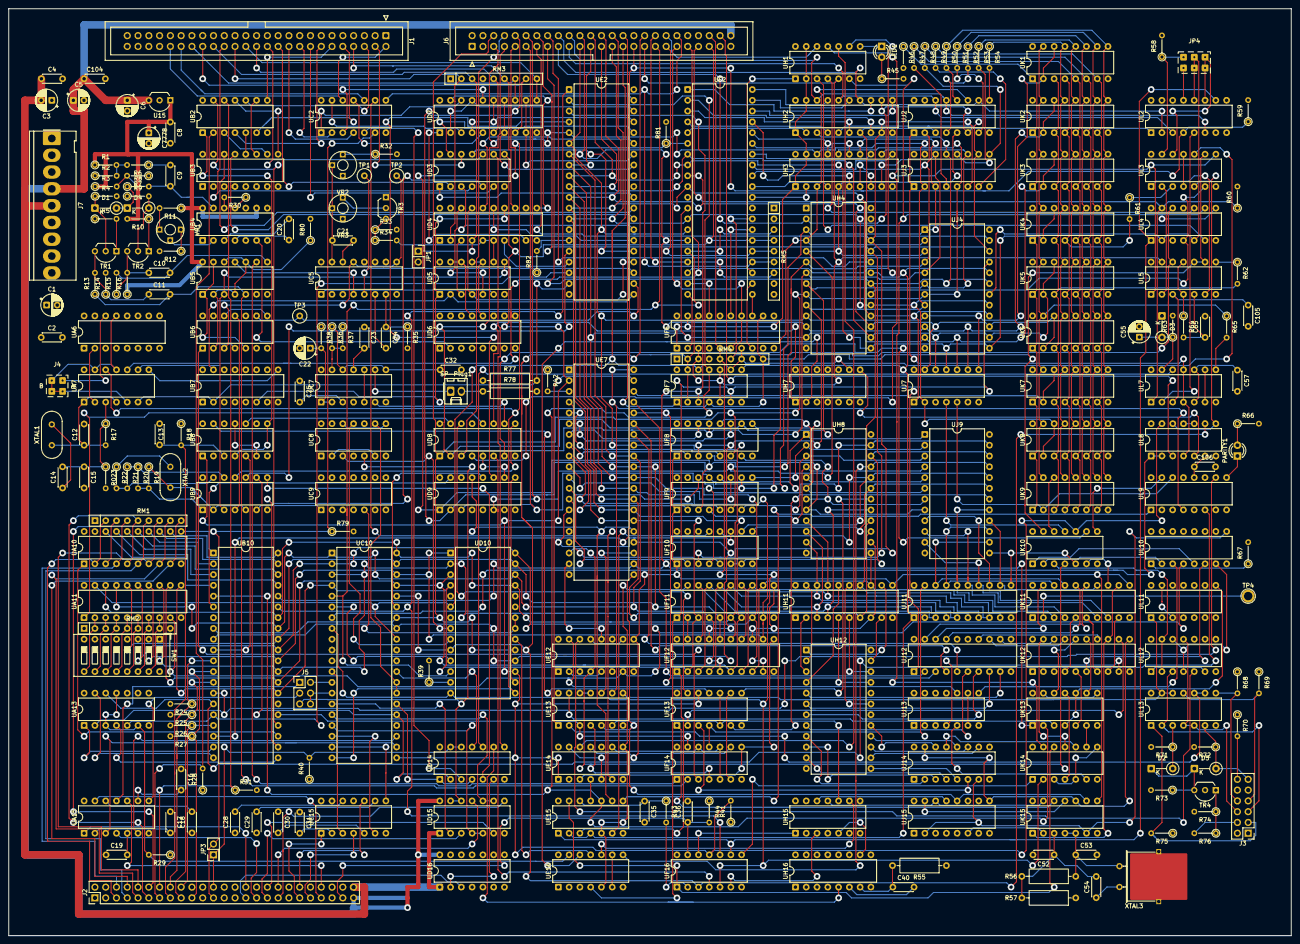
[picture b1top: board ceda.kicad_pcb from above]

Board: 4 copper layers, 302.3 x 218.4 mm, 260 parts (0 on the bottom side), 529 nets.
